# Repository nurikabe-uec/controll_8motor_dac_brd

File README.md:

View this project on [CADLAB.io](https://cadlab.io/project/2098). 
(試しに，CADLABと統合(integrate)してみた)

# controll_8motor_dac_brd

- <span style="color:red; font-size: 20px"> この基板はバグがあるのでまだ使えない </span>
  - 配線ミス (なおしたか覚えてないので書いておきます)
  - モータを回すのに電源が足りない
  - マイコンとジャンパーでつながないといけないので設計として修正しなければならない
- とりあえず，張さんと内藤さんが作ってくれた回路を基板化したものです (モータ8個)
- フォトインタラプタ用に DCジャックを付けていますが，これは 16個用でもう一つの基盤(ここでは1列は 16個のピンなので 基板を2枚使うという想定)と接続する必要がある．
  - その場しのぎとはいえ，恥ずかしい設計で申し訳ないです．

## 理想

- 本来は，1列に対して，一つの電源供給で済ませたい
  - もっと欲を言えば，装置に対して1本電源を挿せば動くようになってほしい

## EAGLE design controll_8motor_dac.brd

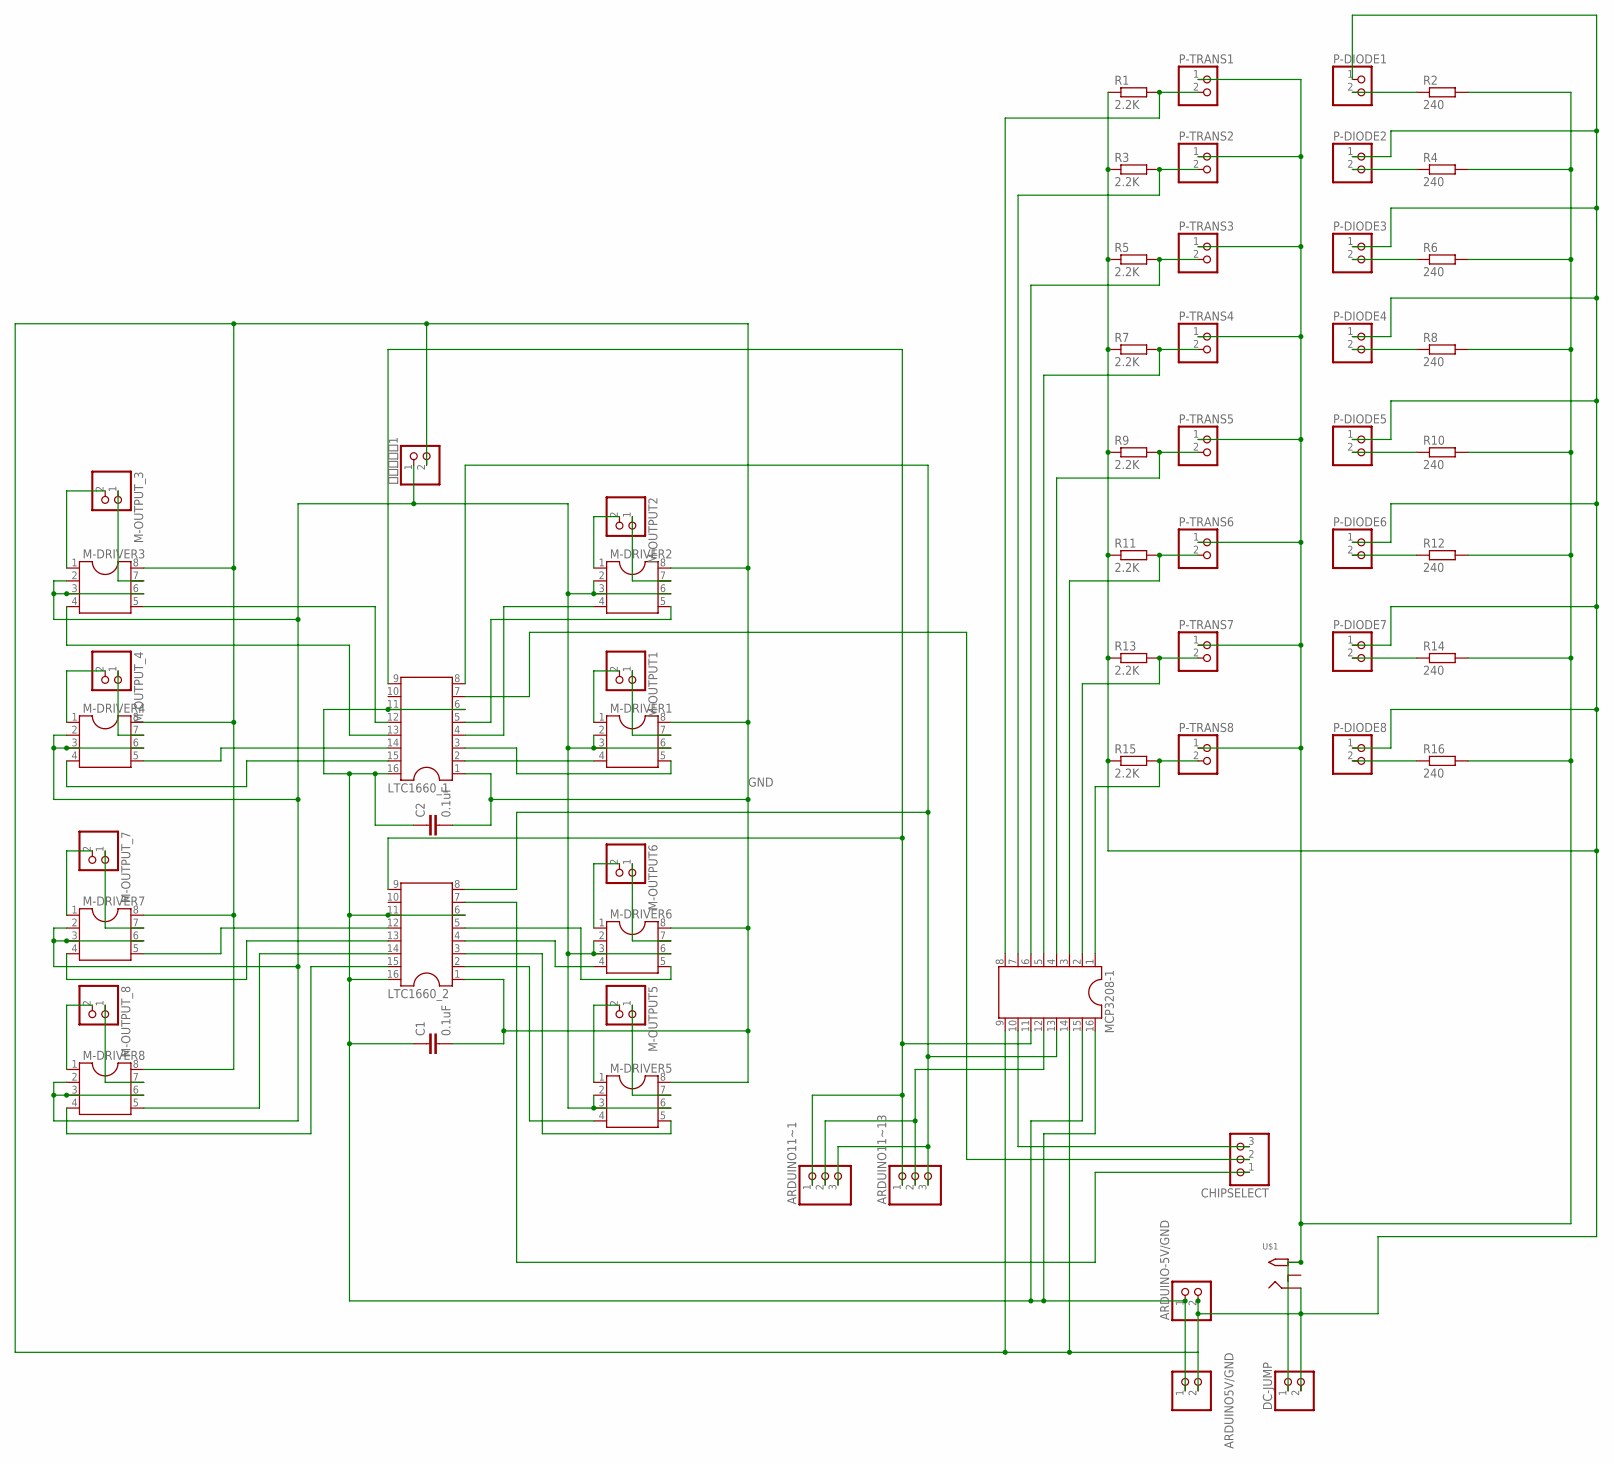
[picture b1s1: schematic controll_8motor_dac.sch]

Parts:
ARDUINO5V/GND: PINHD-1X2; 1X02
ARDUINO11~1, ARDUINO11~13: PINHD-1X3; 1X03
ARDUINO-5V/GND: PINHD-1X2; 1X02
C1, C2: 0.1uF; C025-024X044
CHIPSELECT: PINHD-1X3; 1X03
DC-JUMP: PINHD-1X2; 1X02
LTC1660_1, LTC1660_2: DIL16S; SOCKET-16
M-DRIVER1, M-DRIVER2, M-DRIVER3, M-DRIVER4, M-DRIVER5, M-DRIVER6, M-DRIVER7, M-DRIVER8: DIL8S; SOCKET-08
M-OUTPUT1, M-OUTPUT2, M-OUTPUT5, M-OUTPUT6: PINHD-1X2; 1X02
M-OUTPUT_3, M-OUTPUT_4, M-OUTPUT_7, M-OUTPUT_8: PINHD-1X2; 1X02
MCP3208‐1: DIL16S; SOCKET-16
P-DIODE1, P-DIODE2, P-DIODE3, P-DIODE4, P-DIODE5, P-DIODE6, P-DIODE7, P-DIODE8: PINHD-1X2; 1X02
P-TRANS1, P-TRANS2, P-TRANS3, P-TRANS4, P-TRANS5, P-TRANS6, P-TRANS7, P-TRANS8: PINHD-1X2; 1X02
R1, R3, R5, R7, R9, R11, R13, R15: 2.2K; 0204V
R2, R4, R6, R8, R10, R12, R14, R16: 240; 0204V
U$1: 2.1MMJACKTHM; PJ-102A
安定化電源1: PINHD-1X2; 1X02

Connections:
ARDUINO-5V/GND: ARDUINO5V/GND.1, ARDUINO-5V/GND.1, C1.1, C2.1, LTC1660_1.6, LTC1660_1.11, LTC1660_1.16, LTC1660_2.6, LTC1660_2.11, LTC1660_2.16, MCP3208‐1.15, MCP3208‐1.16
GND: ARDUINO5V/GND.2, ARDUINO-5V/GND.2, C1.2, C2.2, DC-JUMP.2, LTC1660_1.1, LTC1660_2.1, M-DRIVER1.8, M-DRIVER2.8, M-DRIVER3.8, M-DRIVER4.8, M-DRIVER5.8, M-DRIVER6.8, M-DRIVER7.8, M-DRIVER8.8, MCP3208‐1.9, MCP3208‐1.14, P-DIODE1.1, P-DIODE2.1, P-DIODE3.1, P-DIODE4.1, P-DIODE5.1, P-DIODE6.1, P-DIODE7.1, P-DIODE8.1, R1.1, R3.1, R5.1, R7.1, R9.1, R11.1, R13.1, R15.1, U$1.RING, 安定化電源1.2
unnamed: LTC1660_1.12, M-DRIVER3.5
unnamed: M-DRIVER3.1, M-OUTPUT_3.2
unnamed: LTC1660_1.13, M-DRIVER3.4
unnamed: LTC1660_1.15, M-DRIVER4.4
unnamed: LTC1660_2.12, M-DRIVER7.5
unnamed: LTC1660_2.13, M-DRIVER7.4
unnamed: LTC1660_2.14, M-DRIVER8.5
unnamed: LTC1660_2.15, M-DRIVER8.4
unnamed: LTC1660_1.5, M-DRIVER2.5
unnamed: LTC1660_1.4, M-DRIVER2.4
unnamed: LTC1660_1.3, M-DRIVER1.5
unnamed: LTC1660_1.2, M-DRIVER1.4
unnamed: M-DRIVER5.1, M-OUTPUT5.2
unnamed: LTC1660_2.4, M-DRIVER6.4
unnamed: LTC1660_2.3, M-DRIVER5.5
unnamed: LTC1660_2.2, M-DRIVER5.4
unnamed: M-DRIVER3.7, M-OUTPUT_3.1
unnamed: M-DRIVER4.7, M-OUTPUT_4.1
unnamed: M-DRIVER4.1, M-OUTPUT_4.2
unnamed: M-DRIVER7.7, M-OUTPUT_7.1
unnamed: M-DRIVER7.1, M-OUTPUT_7.2
unnamed: M-DRIVER8.7, M-OUTPUT_8.1
unnamed: M-DRIVER8.1, M-OUTPUT_8.2
unnamed: M-DRIVER1.7, M-OUTPUT1.1
unnamed: ARDUINO11~1.1, ARDUINO11~13.1, LTC1660_1.9, LTC1660_2.9, MCP3208‐1.11
unnamed: LTC1660_1.14, M-DRIVER4.5
unnamed: M-DRIVER2.7, M-OUTPUT2.1
unnamed: M-DRIVER2.1, M-OUTPUT2.2
unnamed: LTC1660_2.5, M-DRIVER6.5
unnamed: M-DRIVER5.7, M-OUTPUT5.1
unnamed: M-DRIVER6.1, M-OUTPUT6.2
unnamed: M-DRIVER6.7, M-OUTPUT6.1
unnamed: M-DRIVER1.2, M-DRIVER1.3, M-DRIVER1.6, M-DRIVER2.2, M-DRIVER2.3, M-DRIVER2.6, M-DRIVER3.2, M-DRIVER3.3, M-DRIVER3.6, M-DRIVER4.2, M-DRIVER4.3, M-DRIVER4.6, M-DRIVER5.2, M-DRIVER5.3, M-DRIVER5.6, M-DRIVER6.2, M-DRIVER6.3, M-DRIVER6.6, M-DRIVER7.2, M-DRIVER7.3, M-DRIVER7.6, M-DRIVER8.2, M-DRIVER8.3, M-DRIVER8.6, 安定化電源1.1
unnamed: ARDUINO11~1.3, ARDUINO11~13.3, LTC1660_1.8, LTC1660_2.8, MCP3208‐1.13
unnamed: CHIPSELECT.2, LTC1660_1.7
unnamed: M-DRIVER1.1, M-OUTPUT1.2
unnamed: CHIPSELECT.1, LTC1660_2.7
unnamed: ARDUINO11~1.2, ARDUINO11~13.2, MCP3208‐1.12
unnamed: P-DIODE8.2, R16.1
unnamed: CHIPSELECT.3, MCP3208‐1.10
unnamed: P-DIODE7.2, R14.1
unnamed: P-DIODE6.2, R12.1
unnamed: P-DIODE5.2, R10.1
unnamed: P-DIODE4.2, R8.1
unnamed: P-DIODE3.2, R6.1
unnamed: P-DIODE2.2, R4.1
unnamed: P-DIODE1.2, R2.1
unnamed: MCP3208‐1.7, P-TRANS2.2, R3.2
unnamed: MCP3208‐1.8, P-TRANS1.2, R1.2
unnamed: MCP3208‐1.6, P-TRANS3.2, R5.2
unnamed: MCP3208‐1.5, P-TRANS4.2, R7.2
unnamed: MCP3208‐1.4, P-TRANS5.2, R9.2
unnamed: MCP3208‐1.3, P-TRANS6.2, R11.2
unnamed: MCP3208‐1.2, P-TRANS7.2, R13.2
unnamed: MCP3208‐1.1, P-TRANS8.2, R15.2
unnamed: DC-JUMP.1, P-TRANS1.1, P-TRANS2.1, P-TRANS3.1, P-TRANS4.1, P-TRANS5.1, P-TRANS6.1, P-TRANS7.1, P-TRANS8.1, R2.2, R4.2, R6.2, R8.2, R10.2, R12.2, R14.2, R16.2, U$1.TIP

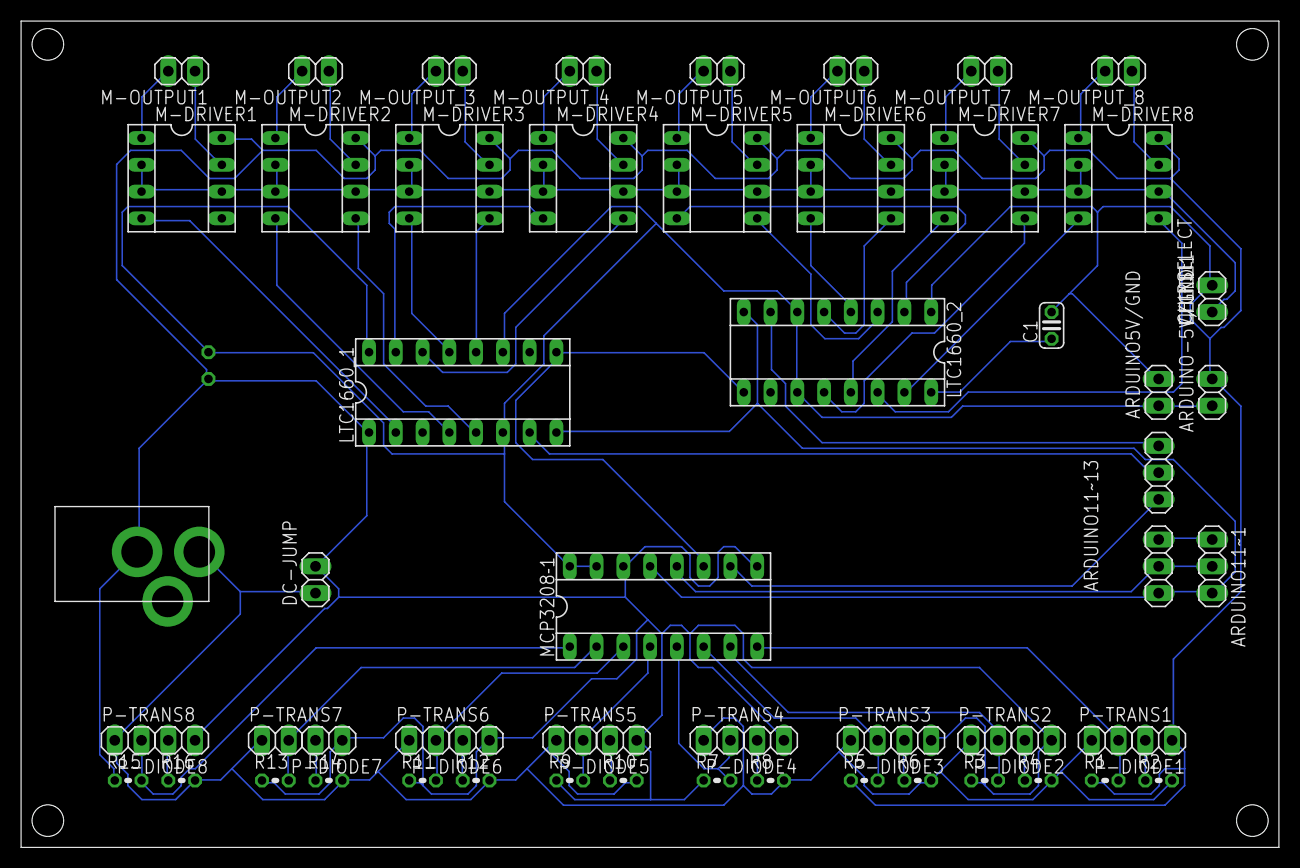
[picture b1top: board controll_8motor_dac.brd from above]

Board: 2 copper layers, 119.4 x 78.4 mm, 61 parts (1 on the bottom side), 58 nets.

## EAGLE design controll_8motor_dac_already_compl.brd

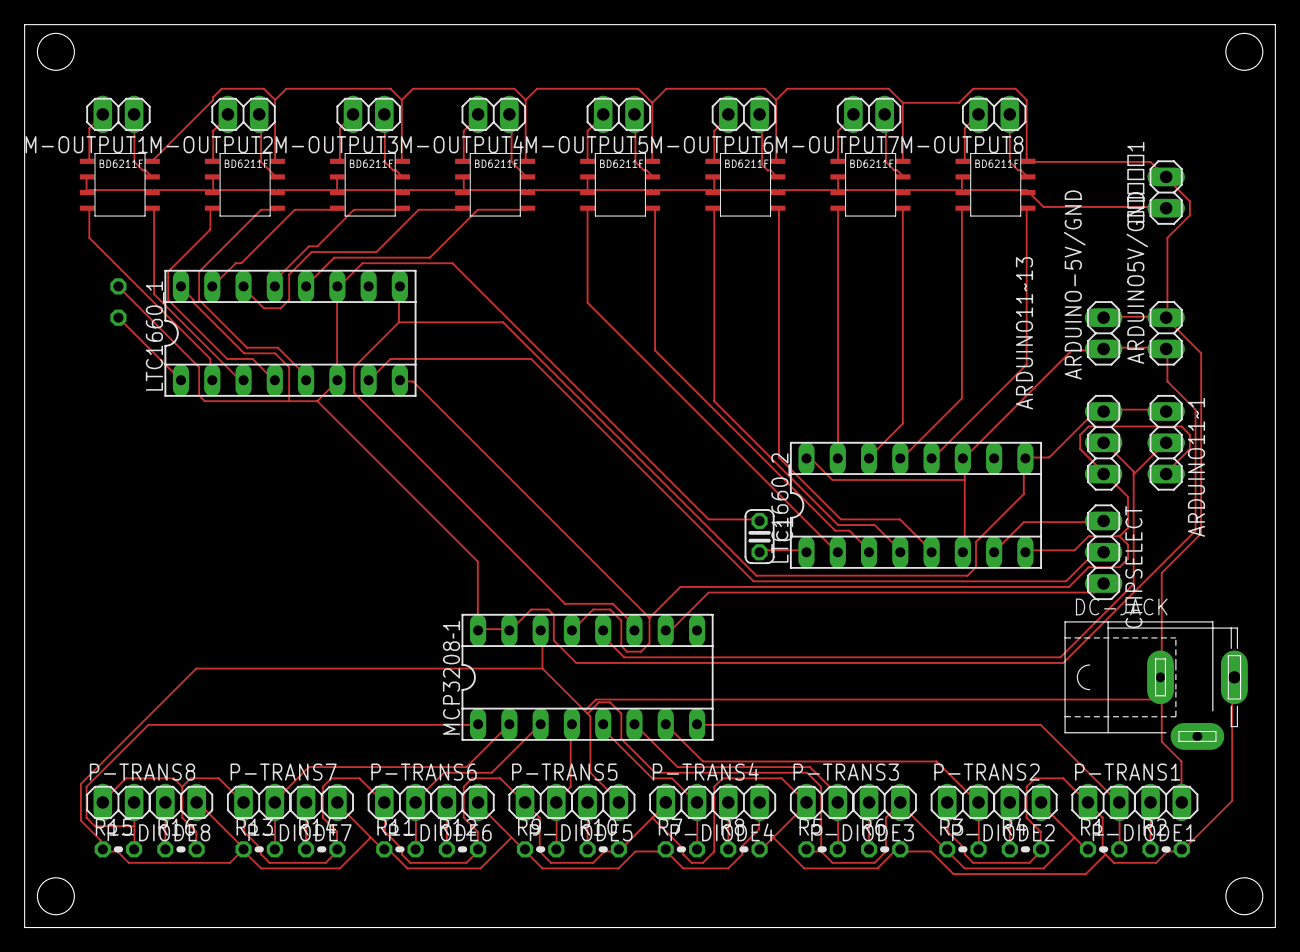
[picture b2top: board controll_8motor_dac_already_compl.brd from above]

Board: 2 copper layers, 101.6 x 73.3 mm, 60 parts (1 on the bottom side), 60 nets.

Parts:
ARDUINO5V/GND: 1X02
ARDUINO11~1, ARDUINO11~13: 1X03
ARDUINO-5V/GND: 1X02
C1, C2: 0.1uF; C025-024X044
CHIPSELECT: 1X03
DC-JACK: SPC4077
LTC1660_1, LTC1660_2: SOCKET-16
M-DRIVER_1, M-DRIVER_2, M-DRIVER_3, M-DRIVER_4, M-DRIVER_5, M-DRIVER_6, M-DRIVER_7, M-DRIVER_8: BD6211F-E2
M-OUTPUT1, M-OUTPUT2, M-OUTPUT3, M-OUTPUT4, M-OUTPUT5, M-OUTPUT6, M-OUTPUT7, M-OUTPUT8: 1X02
MCP3208‐1: SOCKET-16
P-DIODE1, P-DIODE2, P-DIODE3, P-DIODE4, P-DIODE5, P-DIODE6, P-DIODE7, P-DIODE8: 1X02
P-TRANS1, P-TRANS2, P-TRANS3, P-TRANS4, P-TRANS5, P-TRANS6, P-TRANS7, P-TRANS8: 1X02
R1, R3, R5, R7, R9, R11, R13, R15: 2.2K; 0204V
R2, R4, R6, R8, R10, R12, R14, R16: 240; 0204V
安定化電源1: 1X02

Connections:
ARDUINO-5V/GND: ARDUINO5V/GND.1, ARDUINO-5V/GND.1, C1.1, C2.1, LTC1660_1.6, LTC1660_1.11, LTC1660_1.16, LTC1660_2.6, LTC1660_2.11, LTC1660_2.16, MCP3208‐1.15, MCP3208‐1.16
unnamed: LTC1660_1.12, M-DRIVER_4.5
unnamed: M-DRIVER_4.1, M-OUTPUT4.2
unnamed: LTC1660_1.14, M-DRIVER_4.4
unnamed: LTC1660_1.15, M-DRIVER_3.4
unnamed: LTC1660_2.12, M-DRIVER_8.5
unnamed: LTC1660_2.13, M-DRIVER_8.4
unnamed: LTC1660_2.14, M-DRIVER_7.5
unnamed: LTC1660_2.15, M-DRIVER_7.4
unnamed: LTC1660_1.5, M-DRIVER_2.5
unnamed: LTC1660_1.4, M-DRIVER_2.4
unnamed: LTC1660_1.3, M-DRIVER_1.5
unnamed: LTC1660_1.2, M-DRIVER_1.4
unnamed: M-DRIVER_5.1, M-OUTPUT5.2
unnamed: LTC1660_2.4, M-DRIVER_6.4
unnamed: LTC1660_2.3, M-DRIVER_5.5
unnamed: LTC1660_2.2, M-DRIVER_5.4
unnamed: M-DRIVER_4.7, M-OUTPUT4.1
unnamed: M-DRIVER_3.7, M-OUTPUT3.1
unnamed: M-DRIVER_3.1, M-OUTPUT3.2
unnamed: M-DRIVER_8.7, M-OUTPUT8.1
unnamed: M-DRIVER_8.1, M-OUTPUT8.2
unnamed: M-DRIVER_7.7, M-OUTPUT7.1
unnamed: M-DRIVER_7.1, M-OUTPUT7.2
unnamed: M-DRIVER_1.7, M-OUTPUT1.1
unnamed: ARDUINO11~1.1, ARDUINO11~13.1, LTC1660_1.9, LTC1660_2.9, MCP3208‐1.11
unnamed: LTC1660_1.13, M-DRIVER_3.5
unnamed: M-DRIVER_2.7, M-OUTPUT2.1
unnamed: M-DRIVER_2.1, M-OUTPUT2.2
unnamed: LTC1660_2.5, M-DRIVER_6.5
unnamed: M-DRIVER_5.7, M-OUTPUT5.1
unnamed: M-DRIVER_6.1, M-OUTPUT6.2
unnamed: M-DRIVER_6.7, M-OUTPUT6.1
unnamed: M-DRIVER_1.2, M-DRIVER_1.3, M-DRIVER_1.6, M-DRIVER_2.2, M-DRIVER_2.3, M-DRIVER_2.6, M-DRIVER_3.2, M-DRIVER_3.3, M-DRIVER_3.6, M-DRIVER_4.2, M-DRIVER_4.3, M-DRIVER_4.6, M-DRIVER_5.2, M-DRIVER_5.3, M-DRIVER_5.6, M-DRIVER_6.2, M-DRIVER_6.3, M-DRIVER_6.6, M-DRIVER_7.2, M-DRIVER_7.3, M-DRIVER_7.6, M-DRIVER_8.2, M-DRIVER_8.3, M-DRIVER_8.6, 安定化電源1.1
unnamed: C2.2, LTC1660_1.1
unnamed: C1.2, LTC1660_2.1
unnamed: ARDUINO11~1.3, ARDUINO11~13.3, LTC1660_1.8, LTC1660_2.8, MCP3208‐1.13
unnamed: CHIPSELECT.2, LTC1660_1.7
unnamed: M-DRIVER_1.1, M-OUTPUT1.2
unnamed: CHIPSELECT.1, LTC1660_2.7
unnamed: ARDUINO11~1.2, ARDUINO11~13.2, MCP3208‐1.12
unnamed: P-DIODE8.2, R16.1
unnamed: CHIPSELECT.3, MCP3208‐1.10
unnamed: P-DIODE7.2, R14.1
unnamed: P-DIODE6.2, R12.1
unnamed: P-DIODE5.2, R10.1
unnamed: P-DIODE4.2, R8.1
unnamed: P-DIODE3.2, R6.1
unnamed: P-DIODE2.2, R4.1
unnamed: P-DIODE1.2, R2.1
unnamed: MCP3208‐1.7, P-TRANS2.2, R3.2
unnamed: MCP3208‐1.8, P-TRANS1.2, R1.2
unnamed: MCP3208‐1.6, P-TRANS3.2, R5.2
unnamed: MCP3208‐1.5, P-TRANS4.2, R7.2
unnamed: MCP3208‐1.4, P-TRANS5.2, R9.2
unnamed: MCP3208‐1.3, P-TRANS6.2, R11.2
unnamed: MCP3208‐1.2, P-TRANS7.2, R13.2
unnamed: MCP3208‐1.1, P-TRANS8.2, R15.2
unnamed: DC-JACK.3, P-TRANS1.1, P-TRANS2.1, P-TRANS3.1, P-TRANS4.1, P-TRANS5.1, P-TRANS6.1, P-TRANS7.1, P-TRANS8.1, R2.2, R4.2, R6.2, R8.2, R10.2, R12.2, R14.2, R16.2
P-DIORD1: ARDUINO5V/GND.2, ARDUINO-5V/GND.2, DC-JACK.1, M-DRIVER_1.8, M-DRIVER_2.8, M-DRIVER_3.8, M-DRIVER_4.8, M-DRIVER_5.8, M-DRIVER_6.8, M-DRIVER_7.8, M-DRIVER_8.8, MCP3208‐1.9, MCP3208‐1.14, P-DIODE1.1, P-DIODE2.1, P-DIODE3.1, P-DIODE4.1, P-DIODE5.1, P-DIODE6.1, P-DIODE7.1, P-DIODE8.1, R1.1, R3.1, R5.1, R7.1, R9.1, R11.1, R13.1, R15.1, 安定化電源1.2

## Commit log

2019-08-28 start git version control
2019-08-28 version1 できた． なかなか配線がやばいものだなぁ．
2019-08-28 BD6211F-E2 の大きさを変更
2019-08-29 backup before copy
2019-08-29 竹内君が配線してくれたバージョン．回路図は変わってない 100 % になってるよ！ DCジャックの向きが逆
2019-08-29 DCジャックを長穴＆外向きにした
2019-08-30 基板加工機の使い方を間違えていたことに気づいたので DCジャックのつなぎ方を戻した． さらに，このまま掘ってしまうと表面実装がミラーになってしまうのでこれから 修正する
2019-08-30 変換基盤を乗せるバージョン．(まだ微妙に刺さらない) - モータドライバ壊れた時ように変換基盤付けたほうがよいよというアドバイスを受けて
2019-08-30 配線してみた,icパーツ使ってみた
2019-09-07 配線しなおし
2019-09-07 Backlink to CADLAB.io has been added.
2019-09-07 READM更新
